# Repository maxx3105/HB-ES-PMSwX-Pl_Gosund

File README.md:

# HB-ES-PMSwX-Pl_Gosund
Umbau [Gosund SP112 und Baugleiche](https://gosund-deutschland.de/Gosund-SP112-Zwischenstecker-mit-2-x-USB-Typ-F-Schuko-WiFi) zu HB-ES-PMSw2-Pl_SP112.

Umbau [Gosund SP211 und Baugleiche](https://de.gosund.com/products/gosund%E2%84%A2-smart-wlan-steckdose-sp211?spm=..product.header_1.1&spm_prev=..collection.collection_detail_1.1) zu HB-ES-PMSw2-Pl_SP211.

Umbau [Gosund P1 3-fach Stecker und Baugleiche](https://de.gosund.com/products/gosund%E2%84%A2-smart-wlan-steckdosenleiste-p1?spm=..collection.collection_detail_1.1&spm_prev=..collection.header_1.1) zu HB-ES-PMSw3-Pl_P1.

Dieses Projekt basiert auf der Arbeit von [pa-pa](https://github.com/pa-pa/AskSinPP) ,[Jérôme](https://github.com/jp112sdl/Beispiel_AskSinPP) und [Asselhead](https://github.com/Asselhead/Arduino-Pro-Mini-RF).

Angelehnt an das Projekt von [stan23](https://github.com/stan23/HM-ES-PMSw1-Pl_GosundSP1).

# Hardware

### Bauteile

Bauteile                   | Bezeichnung          | Anzahl | Kommentar   | LCSC   |
-------------------------- | -------------------- | ------ | ----------- | ------ |
C1                         | 10uF, +-20%, 6,3V    |   1    | G0402       | C76991 |
C23                        | 4.7uF 10V            |   1    | G0402       | C23733 |
C2, C3, C4, C5             | 100nF, 10%, 16V      |        |             |        |
C41, C51, C91, C111        | 100nF, 10%, 16V      |        |             |        |
C141, C151, C181           | 100nF, 10%, 16V      |   11   | G0402       | C1525  |
C124                       | 100pF, 5%, 50V       |   1    | G0402       | C1546  |
C81                        | 12pF, 5%, 50V        |   1    | G0402       | C1547  |
C101                       | 15pF, 5%, 50V        |   1    | G0402       | C1548  |
C121                       | 1pF, +-0.25pF, 50V   |   1    | G0402       | C1550  |
C122, C131                 | 1.5pF, +-0.25pF, 50V |   1    | G0402       | C1552  |
C123                       | 3.3pF, +-0.25pF, 50V |   1    | G0402       | C1565  |
DR121, DR123, DR124, DR131 | 12nH, 5%             |   4    | G0402       | C24563 |
DR122, DR132               | 18nH, 5%             |   2    | G0402       | C24562 |
R1                         | 10K                  |   1    | G0402       | C25744 |
R171                       | 56K                  |   1    | G0402       | C25796 |
U1                         | ATMEGA 644PA-MU      |   1    | QFN-44      | C614419|
U2                         | CC1101               |   1    | QFN-20      | C29953 |
Q1                         | RESONATORS 26MHZ     |   1    | SMD-3225_4P | C91747 |

#### Sonstiges

~8,3 cm Draht als Antenne

### Programmieradapter
- 1x ISP (z.B. [diesen hier](https://www.diamex.de/dxshop/USB-ISP-Programmer-fuer-Atmel-AVR-Rev2))

# Software

### Fuses
Ext:  0xFF
High: 0xD2
Low:  0xE2

`C:\Program Files (x86)\Arduino\hardware\tools\avr\bin> .\avrdude -C ..\etc\avrdude.conf -p m644p -P com7 -c stk500 -U lfuse:w:0xE2:m -U hfuse:w:0xD2:m -U efuse:w:0xFF:m`

### Firmware

Projektverzeichnis: [HB-ES-PMSw1-Pl_GosundSP1](coming soon)

Benötigt werden die Bibliotheken [AskSinPP](https://github.com/pa-pa/AskSinPP) aus dem master-Branch, sowie die [HLW8012](https://github.com/xoseperez/hlw8012), die [MightyCore](https://github.com/MCUdude/MightyCore), die [EnableInterrupt](https://github.com/GreyGnome/EnableInterrupt) und [Low-Power](https://github.com/rocketscream/Low-Power).

# Bauanleitung

coming soon

# Kalibrierung

coming soon

# Bilder

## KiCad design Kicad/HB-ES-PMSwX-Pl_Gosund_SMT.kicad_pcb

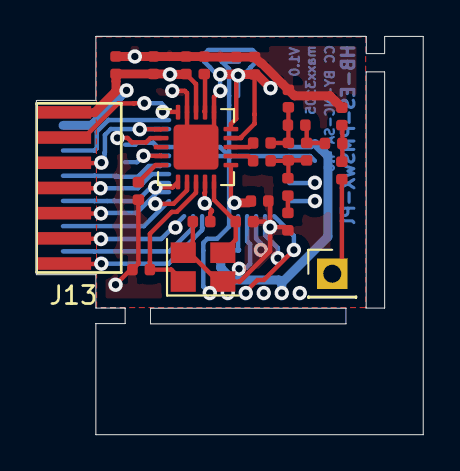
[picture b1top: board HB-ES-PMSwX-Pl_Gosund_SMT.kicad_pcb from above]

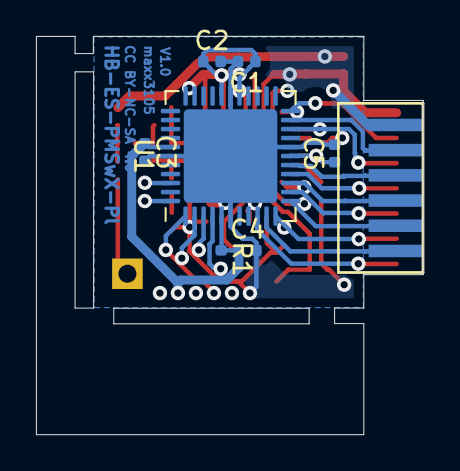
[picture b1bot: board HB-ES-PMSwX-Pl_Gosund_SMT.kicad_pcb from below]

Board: 4 copper layers, 21.5 x 22.1 mm, 33 parts (7 on the bottom side), 31 nets.

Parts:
C1: 10uF, +-20%, 6.3V; C_0402_1005Metric
C2, C3, C4, C5, C41, C51, C91, C111, C141, C151, C181: 100nF, 10%, 16V; C_0402_1005Metric
C23: 4.7uF, 10V; C_0402_1005Metric
C81: 12pF, 5%, 50V; C_0402_1005Metric
C101: 15pF, 5%, 50V; C_0402_1005Metric
C121: 1pF, +-0.25pF, 50V; C_0402_1005Metric
C122, C131: 1.5pF, +-0.25pF, 50V; C_0402_1005Metric
C123: 3.3pF, +-0.25pF, 50V; C_0402_1005Metric
C124: 100pF, 5%, 50V; C_0402_1005Metric
DR121, DR123, DR124, DR131: 12nH, 5%; L_0402_1005Metric
DR122, DR132: 18nH, 5%; L_0402_1005Metric
J1: Conn_01x01; PinHeader_1x01_P2.54mm_Vertical
J13: BW_Gosund_Con_V2; Gosund_SP111-C_V1.0
Q1: 26Mhz, +-10PPM, 10pF; Crystal_SMD_SeikoEpson_TSX3225-4Pin_3.2x2.5mm
R1: 10k; R_0402_1005Metric
R171: 56K; R_0402_1005Metric
U1: ATmega644PA-MU; QFN-44-1EP_7x7mm_P0.5mm_EP5.2x5.2mm
U2: CC1101RGPR; QFN-20-1EP_4x4mm_P0.5mm_EP2.5x2.5mm

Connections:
/BUT1: J13.BUT1, U1.13
/BUT2: J13.BUT2, U1.16
/CF: J13.CF, U1.12
/CF1: J13.CF1, U1.11
/CS: U1.44, U2.7
/GDO0: U1.42, U2.6
/LED1: J13.LED1, U1.15
/LED2: J13.LED2, U1.14
/MISO: U1.2, U2.2
/MOSI: U1.1, U2.20
/REL1: J13.REL1, U1.20
/REL2: J13.REL2, U1.21
/RES: J13.RES, U1.22
/RESET: R1.2, U1.4
/RX: J13.RX, U1.9
/SCK: U1.3, U2.1
/TX: J13.TX, U1.10
GND: C1.2, C2.2, C3.2, C4.2, C5.2, C23.2, C41.2, C51.2, C81.2, C91.2, C101.1, C111.2, C123.1, C124.1, C131.1, C141.2, C151.2, C181.2, J13.GND, Q1.2, Q1.4, R171.2, U1.6, U1.18, U1.28, U1.39, U1.45, U2.16, U2.19, U2.21
unnamed: C51.1, U2.5
unnamed: C81.1, Q1.1, U2.8
unnamed: C101.2, Q1.3, U2.10
unnamed: C121.1, C122.1, DR121.1, DR122.1
unnamed: C121.2, C131.2, DR131.1, DR132.2
unnamed: C122.2, DR123.2, DR132.1
unnamed: C123.2, DR123.1, DR124.2
unnamed: C124.2, DR122.2
unnamed: DR121.2, U2.12
unnamed: DR124.1, J1.1
unnamed: DR131.2, U2.13
unnamed: R171.1, U2.17
VCC: C1.1, C2.1, C3.1, C4.1, C5.1, C23.1, C41.1, C91.1, C111.1, C141.1, C151.1, C181.1, J13.VCC, R1.1, U1.5, U1.17, U1.27, U1.29, U1.38, U2.4, U2.9, U2.11, U2.14, U2.15, U2.18

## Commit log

2022-01-18 Bugfix
2022-01-20 C51 bugfix

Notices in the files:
Kicad/HB-ES-PMSwX-Pl_Gosund_SMT.kicad_pcb:
CC BY-NC-SA 4.0
